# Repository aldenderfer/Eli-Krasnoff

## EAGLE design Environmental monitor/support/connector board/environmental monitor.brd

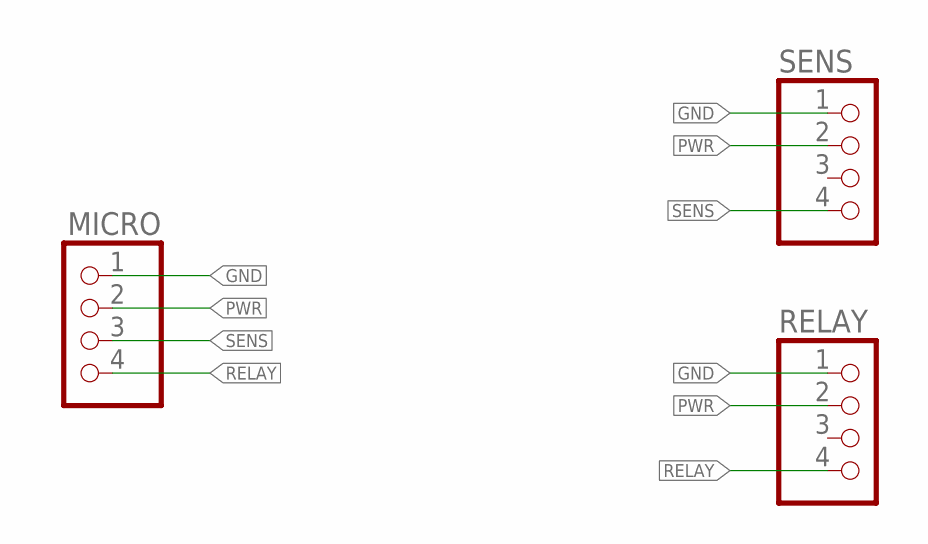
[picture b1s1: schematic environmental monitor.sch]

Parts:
MICRO: PINHD-1X4; 1X04
RELAY: PINHD-1X4; 1X04
SENS: PINHD-1X4; 1X04

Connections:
GND: MICRO.1, RELAY.1, SENS.1
PWR: MICRO.2, RELAY.2, SENS.2
RELAY: MICRO.4, RELAY.4
SENS: MICRO.3, SENS.4

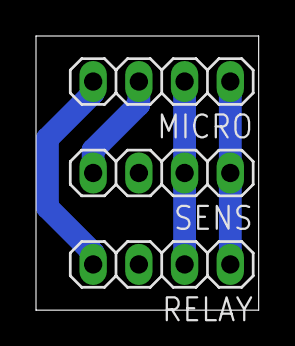
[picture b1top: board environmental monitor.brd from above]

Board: 2 copper layers, 12.4 x 15.2 mm, 3 parts (0 on the bottom side), 4 nets.

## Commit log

2015-12-16 added illustrator design
2015-12-17 added code
    This is Elis first commit.
2015-12-23 revised ai design
2016-01-23 updated design file
2016-01-26 added schematic and board design files
2016-05-09 moved everything to one place
2016-05-18 folder restruct; added battery enclosure model
2016-06-29 added all tank code, only missing lightseek mode
2017-04-21 updated some things!
